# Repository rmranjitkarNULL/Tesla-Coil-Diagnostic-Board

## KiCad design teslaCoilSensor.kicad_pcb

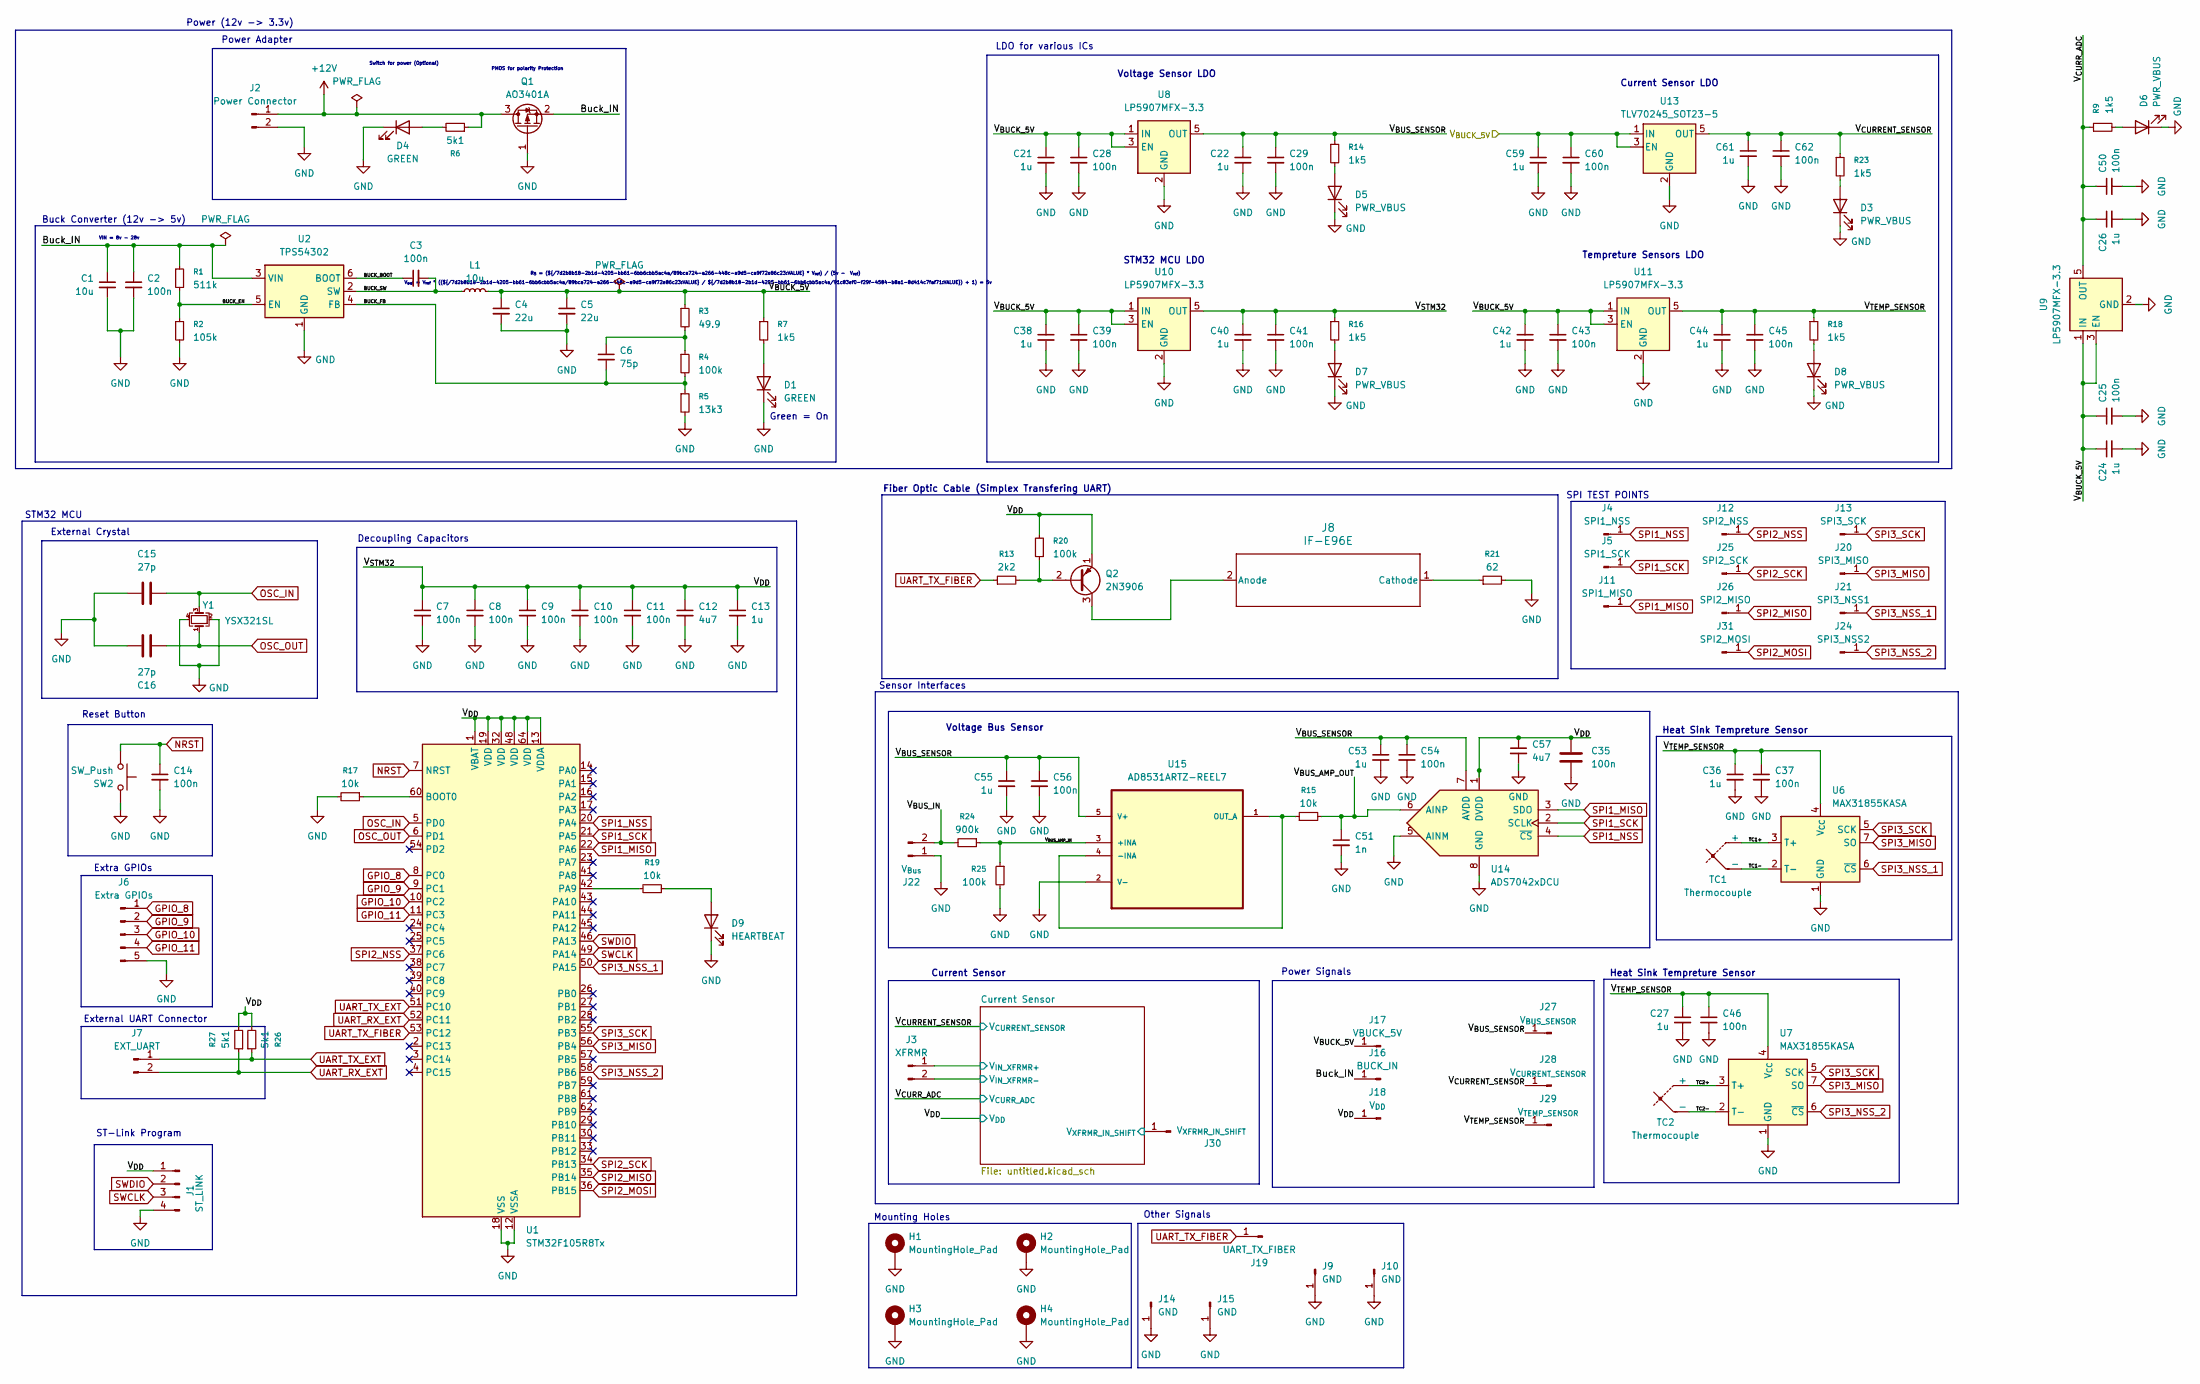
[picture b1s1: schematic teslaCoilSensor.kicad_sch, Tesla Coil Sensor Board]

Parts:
C1: 10u; C_0603_1608Metric
C2, C3, C7, C8, C9, C10, C11, C14, C25, C28, C29, C35, C37, C39, C41, C43, C45, C46, C50, C54, C56, C60, C62: 100n; C_0603_1608Metric
C4, C5: 22u; C_0603_1608Metric
C6: 75p; C_0603_1608Metric
C12, C57: 4u7; C_0603_1608Metric
C13, C21, C22, C24, C26, C27, C36, C38, C40, C42, C44, C53, C55, C59, C61: 1u; C_0603_1608Metric
C15, C16: 27p; C_0603_1608Metric
C51: 1n; C_0603_1608Metric
D1, D4: GREEN; LED_0805_2012Metric
D3, D5, D6, D7, D8: PWR_VBUS; LED_0805_2012Metric
D9: HEARTBEAT; LED_0805_2012Metric
H1, H2, H3, H4: MountingHole_Pad; MountingHole_3.5mm_Pad
J1: ST_LINK; PinHeader_1x04_P2.54mm_Vertical
J2: Power Connector; TerminalBlock_Phoenix_MPT-0,5-2-2.54_1x02_P2.54mm_Horizontal
J3: XFRMR; TerminalBlock_Phoenix_MPT-0,5-2-2.54_1x02_P2.54mm_Horizontal
J4: SPI1_NSS; PinHeader_1x01_P2.54mm_Vertical
J5: SPI1_SCK; PinHeader_1x01_P2.54mm_Vertical
J6: Extra GPIOs; PinHeader_1x05_P2.54mm_Vertical
J7: EXT_UART; TerminalBlock_Phoenix_MPT-0,5-2-2.54_1x02_P2.54mm_Horizontal
J8: IF-E96E; IF-E96E_IFB
J9, J10, J14, J15: GND; PinHeader_1x01_P2.54mm_Vertical
J11: SPI1_MISO; PinHeader_1x01_P2.54mm_Vertical
J12: SPI2_NSS; PinHeader_1x01_P2.54mm_Vertical
J13: SPI3_SCK; PinHeader_1x01_P2.54mm_Vertical
J16: BUCK_IN; PinHeader_1x01_P2.54mm_Vertical
J17: VBUCK_5V; PinHeader_1x01_P2.54mm_Vertical
J18: V_{DD}; PinHeader_1x01_P2.54mm_Vertical
J19: UART_TX_FIBER; PinHeader_1x01_P2.54mm_Vertical
J20: SPI3_MISO; PinHeader_1x01_P2.54mm_Vertical
J21: SPI3_NSS1; PinHeader_1x01_P2.54mm_Vertical
J22: V_{Bus}; TerminalBlock_Phoenix_MPT-0,5-2-2.54_1x02_P2.54mm_Horizontal
J24: SPI3_NSS2; PinHeader_1x01_P2.54mm_Vertical
J25: SPI2_SCK; PinHeader_1x01_P2.54mm_Vertical
J26: SPI2_MISO; PinHeader_1x01_P2.54mm_Vertical
J27: V_{BUS_SENSOR}; PinHeader_1x01_P2.54mm_Vertical
J28: V_{CURRENT_SENSOR}; PinHeader_1x01_P2.54mm_Vertical
J29: V_{TEMP_SENSOR}; PinHeader_1x01_P2.54mm_Vertical
J30: V_{XFRMR_IN_SHIFT}; PinHeader_1x01_P2.54mm_Vertical
J31: SPI2_MOSI; PinHeader_1x01_P2.54mm_Vertical
L1: 10u; SM7850-100MT
Q1: AO3401A; SOT-23
Q2: 2N3906; TO-92_Inline
R1: 511k; R_0603_1608Metric
R2: 105k; R_0603_1608Metric
R3: 49.9; R_0603_1608Metric
R4, R20, R25: 100k; R_0603_1608Metric
R5: 13k3; R_0603_1608Metric
R6, R26, R27: 5k1; R_0603_1608Metric
R7, R9, R14, R16, R18, R23: 1k5; R_0603_1608Metric
R13: 2k2; R_1206_3216Metric
R15, R17, R19: 10k; R_0603_1608Metric
R21: 62; R_0805_2012Metric
R24: 900k; R_Axial_DIN0204_L3.6mm_D1.6mm_P5.08mm_Horizontal
SW2: SW_Push; SW_SPST_PTS647_Sx50
TC1, TC2: Thermocouple; TerminalBlock_Phoenix_MPT-0,5-2-2.54_1x02_P2.54mm_Horizontal
U1: STM32F105R8Tx; LQFP-64_10x10mm_P0.5mm
U2: TPS54302; SOT-23-6
U6, U7: MAX31855KASA; SOIC-8_3.9x4.9mm_P1.27mm
U8, U9, U10, U11: LP5907MFX-3.3; SOT-23-5
U13: TLV70245_SOT23-5; SOT-23-5
U14: ADS7042xDCU; VSSOP-8_2.3x2mm_P0.5mm
U15: AD8531ARTZ-REEL7; SOT95P280X145-5N; MPN AD8531ARTZ-REEL7
Y1: YSX321SL; Crystal_SMD_3225-4Pin_3.2x2.5mm

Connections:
+12V: J2.1, Q1.3 (D), R6.1
/BUCK_BOOT: C3.1, U2.6 (BOOT)
/BUCK_EN: R1.2, R2.1, U2.5 (EN)
/BUCK_FB: C6.2, R4.2, R5.1, U2.4 (FB)
/BUCK_SW: C3.2, L1.1, U2.2 (SW)
/Buck_IN: C1.1, C2.1, J16.1, Q1.2 (S), R1.1, U2.3 (VIN)
/Current Sensor/V_{IN_XFRMR+}: J3.1; also elsewhere on the board
/Current Sensor/V_{XFRMR_IN_SHIFT}: J30.1; also elsewhere on the board
/TC1+: TC1.1 (+), U6.3 (T+)
/TC1-: TC1.2 (-), U6.2 (T-)
/TC2+: TC2.1 (+), U7.3 (T+)
/TC2-: TC2.2 (-), U7.2 (T-)
/V_{BUCK_5V}: C4.1, C5.1, C21.1, C24.1, C25.1, C28.1, C38.1, C39.1, C42.1, C43.1, C59.1, C60.1, J17.1, L1.2, R3.1, R7.1, U8.1 (IN), U8.3 (EN), U9.1 (IN), U9.3 (EN), U10.1 (IN), U10.3 (EN), U11.1 (IN), U11.3 (EN), U13.1 (IN), U13.3 (EN)
/V_{BUS_AMP_IN}: R24.1, R25.1, U15.3 (+INA)
/V_{BUS_AMP_OUT}: C51.1, R15.2, U14.6 (AINP)
/V_{BUS_IN}: J22.2, R24.2
/V_{BUS_SENSOR}: C22.1, C29.1, C53.1, C54.1, C55.1, C56.1, J27.1, R14.1, U8.5 (OUT), U14.7 (AVDD), U15.5 (V+)
/V_{CURRENT_SENSOR}: C61.1, C62.1, J28.1, R23.1, U13.5 (OUT); also elsewhere on the board
/V_{CURR_ADC}: C26.1, C50.1, R9.1, U9.5 (OUT); also elsewhere on the board
/V_{DD}: C7.1, C8.1, C9.1, C10.1, C11.1, C12.1, C13.1, C35.1, C40.1, C41.1, C57.1, J1.1, J18.1, Q2.1 (E), R16.1, R20.2, R26.2, R27.2, U1.1 (VBAT), U1.13 (VDDA), U1.19 (VDD), U1.32 (VDD), U1.48 (VDD), U1.64 (VDD), U10.5 (OUT), U14.1 (DVDD); also elsewhere on the board
/V_{TEMP_SENSOR}: C27.1, C36.1, C37.1, C44.1, C45.1, C46.1, J29.1, R18.1, U6.4 (V_{CC}), U7.4 (V_{CC}), U11.5 (OUT)
GND: C1.2, C2.2, C4.2, C5.2, C7.2, C8.2, C9.2, C10.2, C11.2, C12.2, C13.2, C14.2, C15.1, C16.1, C21.2, C22.2, C24.2, C25.2, C26.2, C27.2, C28.2, C29.2, C35.2, C36.2, C37.2, C38.2, C39.2, C40.2, C41.2, C42.2, C43.2, C44.2, C45.2, C46.2, C50.2, C51.2, C53.2, C54.2, C55.2, C56.2, C57.2, C59.2, C60.2, C61.2, C62.2, D1.1 (K), D3.1 (K), D4.1 (K), D5.1 (K), D6.1 (K), D7.1 (K), D8.1 (K), D9.1 (K), H1.1, H2.1, H3.1, H4.1, J1.4, J2.2, J3.2, J6.5, J9.1, J10.1, J14.1, J15.1, J22.1, Q1.1 (G), R2.2, R5.2, R17.2, R21.2, R25.2, SW2.1, U1.12 (VSSA), U1.18 (VSS), U1.31 (VSS), U1.47 (VSS), U1.63 (VSS), U2.1 (GND), U6.1 (GND), U7.1 (GND), U8.2 (GND), U9.2 (GND), U10.2 (GND), U11.2 (GND), U13.2 (GND), U14.5 (AINM), U14.8 (GND), U15.2 (V-), Y1.2, Y1.4; also elsewhere on the board
GPIO_8: J6.1, U1.8 (PC0)
GPIO_9: J6.2, U1.9 (PC1)
GPIO_10: J6.3, U1.10 (PC2)
GPIO_11: J6.4, U1.11 (PC3)
NRST: C14.1, SW2.2, U1.7 (NRST)
unnamed: C6.1, R3.2, R4.1
unnamed: D1.2 (A), R7.2
unnamed: D3.2 (A), R23.2
unnamed: D4.2 (A), R6.2
unnamed: D5.2 (A), R14.2
unnamed: D6.2 (A), R9.2
unnamed: D7.2 (A), R16.2
unnamed: D8.2 (A), R18.2
unnamed: D9.2 (A), R19.1
unnamed: J8.2 (Anode), Q2.3 (C)
unnamed: J8.1 (Cathode), R21.1
unnamed: Q2.2 (B), R13.2, R20.1
unnamed: R17.1, U1.60 (BOOT0)
unnamed: R19.2, U1.42 (PA9)
unnamed: R15.1, U15.1 (OUT_A), U15.4 (-INA)
OSC_IN: C15.2, U1.5 (PD0), Y1.3
OSC_OUT: C16.2, U1.6 (PD1), Y1.1
SPI1_MISO: J11.1, U1.22 (PA6), U14.3 (SDO)
SPI1_NSS: J4.1, U1.20 (PA4), U14.4 (~CS)
SPI1_SCK: J5.1, U1.21 (PA5), U14.2 (SCLK)
SPI2_MISO: J26.1, U1.35 (PB14); also elsewhere on the board
SPI2_MOSI: J31.1, U1.36 (PB15); also elsewhere on the board
SPI2_NSS: J12.1, U1.37 (PC6); also elsewhere on the board
SPI2_SCK: J25.1, U1.34 (PB13); also elsewhere on the board
SPI3_MISO: J20.1, U1.56 (PB4), U6.7 (SO), U7.7 (SO)
SPI3_NSS_1: J21.1, U1.50 (PA15), U6.6 (~CS)
SPI3_NSS_2: J24.1, U1.58 (PB6), U7.6 (~CS)
SPI3_SCK: J13.1, U1.55 (PB3), U6.5 (SCK), U7.5 (SCK)
SWCLK: J1.3, U1.49 (PA14)
SWDIO: J1.2, U1.46 (PA13)
UART_RX_EXT: J7.2, R27.1, U1.52 (PC11)
UART_TX_EXT: J7.1, R26.1, U1.51 (PC10)
UART_TX_FIBER: J19.1, R13.1, U1.53 (PC12)

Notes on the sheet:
VIN = 8v - 28v
Buck Converter (12v -> 5v)
External UART Connector
Extra GPIOs
Voltage Sensor LDO
STM32 MCU
Tempreture Sensors LDO
PMOS for polarity Protection
ST-Link Program
V_{out} = V_{ref} * ((${/7d2b8b18-2b1d-4205-bb61-6bb6cbb5ac4a/89bca724-a266-448c-a9d5-ca9f72e86c23:VALUE} / ${/7d2b8b18-2b1d-4205-bb61-6bb6cbb5ac4a/91c83ef0-f29f-4584-b8a1-8d414c7faf71:VALUE}) + 1) = 5v
Heat Sink Tempreture Sensor
SPI TEST POINTS
R_{5} = (${/7d2b8b18-2b1d-4205-bb61-6bb6cbb5ac4a/89bca724-a266-448c-a9d5-ca9f72e86c23:VALUE} * V_{ref}) / (5v - V_{ref})
Power (12v -> 3.3v)
Fiber Optic Cable (Simplex Transfering UART)
Mounting Holes
Power Adapter
STM32 MCU LDO
Power Signals
Switch for power (Optional)
Other Signals
Sensor Interfaces
Current Sensor LDO
Current Sensor
External Crystal
LDO for various ICs
Green = On
Reset Button
Decoupling Capacitors
Voltage Bus Sensor

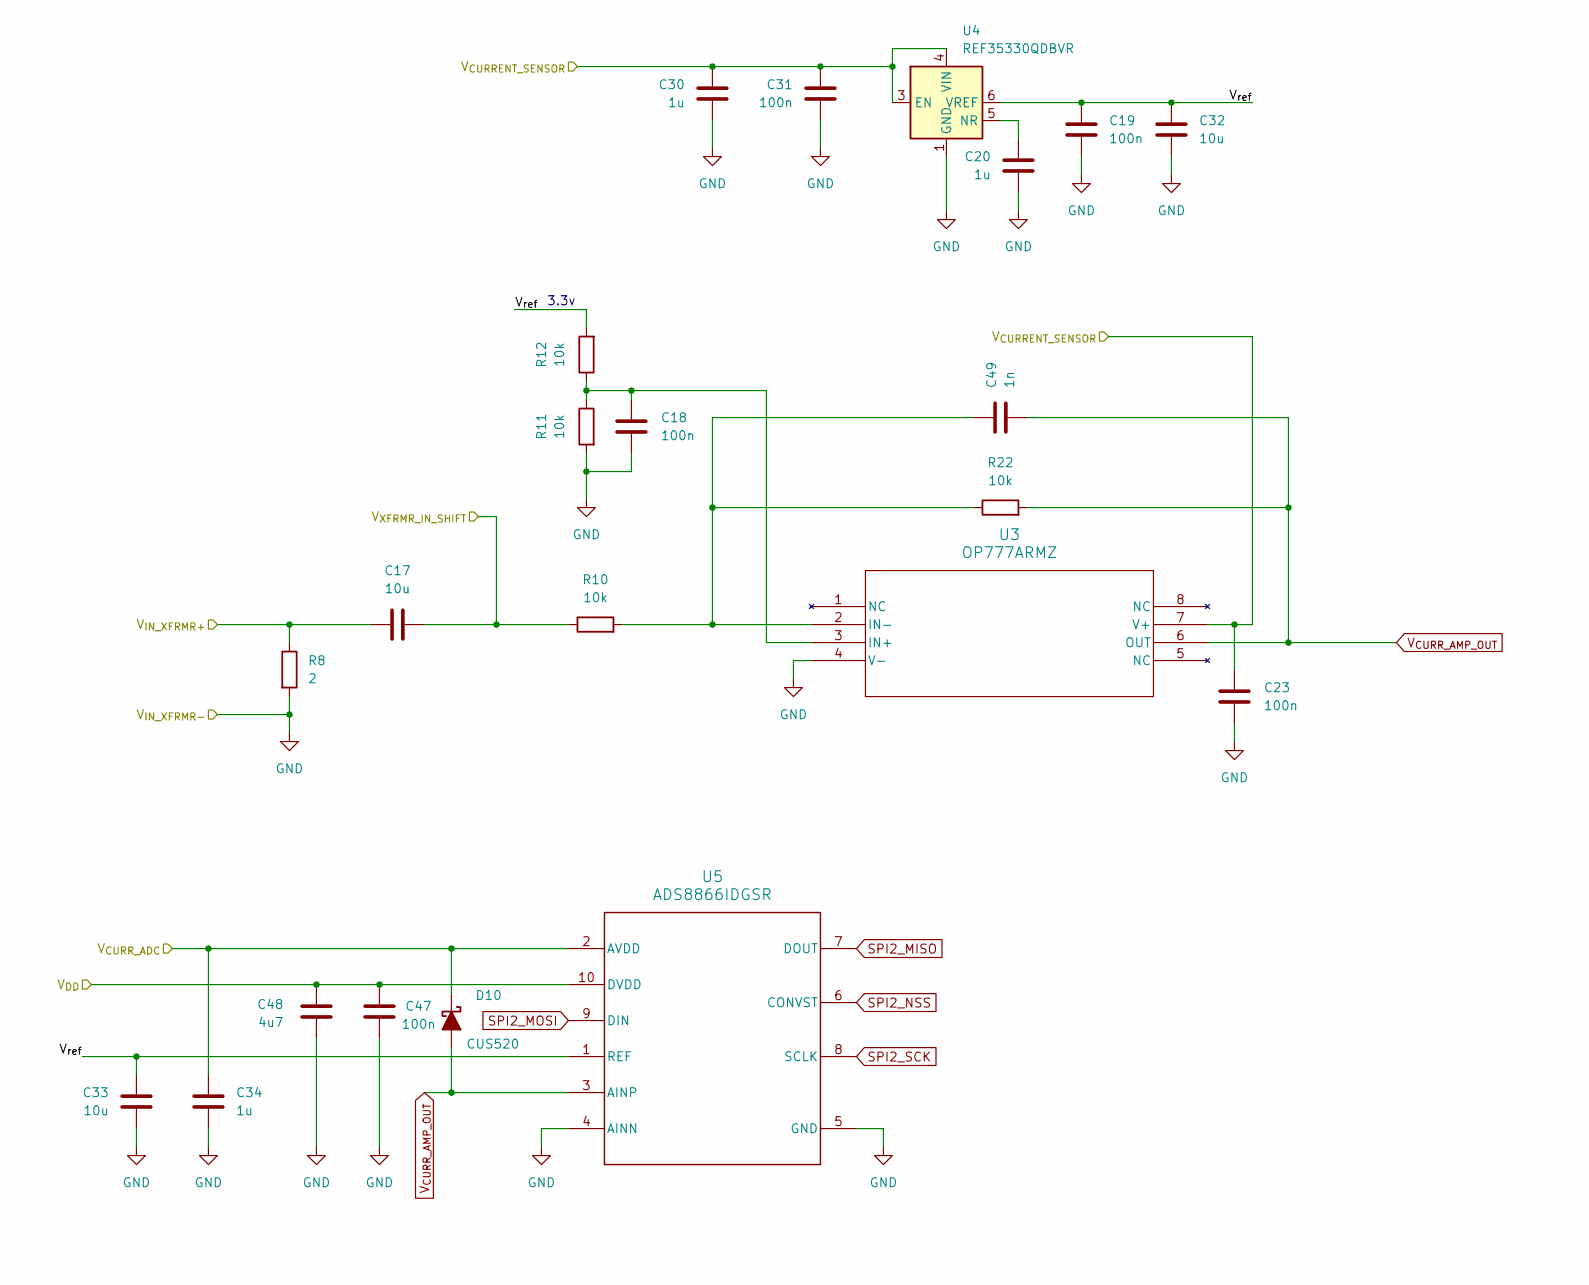
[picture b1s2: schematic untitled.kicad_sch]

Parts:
C17, C32, C33: 10u; C_0603_1608Metric
C18, C19, C23, C31, C47: 100n; C_0603_1608Metric
C20, C30, C34: 1u; C_0603_1608Metric
C48: 4u7; C_0603_1608Metric
C49: 1n; C_0603_1608Metric
D10: CUS520; D_SOD-323
R8: 2; R_1206_3216Metric
R10, R11, R12, R22: 10k; R_0603_1608Metric
U3: OP777ARMZ; R_8_ADI
U4: REF35330QDBVR; SOT-23-6
U5: ADS8866IDGSR; DGS0010A_N

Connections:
/Current Sensor/V_{IN_XFRMR+}: C17.1, R8.1; also elsewhere on the board
/Current Sensor/V_{XFRMR_IN_SHIFT}: C17.2, R10.1; also elsewhere on the board
/Current Sensor/V_{ref}: C19.1, C32.1, C33.1, R12.2, U4.6 (VREF), U5.1 (REF)
/V_{CURRENT_SENSOR}: C23.1, C30.1, C31.1, U3.7 (V+), U4.3 (EN), U4.4 (VIN); also elsewhere on the board
/V_{CURR_ADC}: C34.1, D10.1 (K), U5.2 (AVDD); also elsewhere on the board
/V_{DD}: C47.1, C48.1, U5.10 (DVDD); also elsewhere on the board
GND: C18.2, C19.2, C20.2, C23.2, C30.2, C31.2, C32.2, C33.2, C34.2, C47.2, C48.2, R8.2, R11.2, U3.4 (V-), U4.1 (GND), U4.2 (GND), U5.4 (AINN), U5.5 (GND); also elsewhere on the board
unnamed: C18.1, R11.1, R12.1, U3.3 (IN+)
unnamed: C49.1, R10.2, R22.1, U3.2 (IN-)
unnamed: C20.1, U4.5 (NR)
SPI2_MISO: U5.7 (DOUT); also elsewhere on the board
SPI2_MOSI: U5.9 (DIN); also elsewhere on the board
SPI2_NSS: U5.6 (CONVST); also elsewhere on the board
SPI2_SCK: U5.8 (SCLK); also elsewhere on the board
V_{CURR_AMP_OUT}: C49.2, D10.2 (A), R22.2, U3.6 (OUT), U5.3 (AINP)

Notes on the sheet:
3.3v

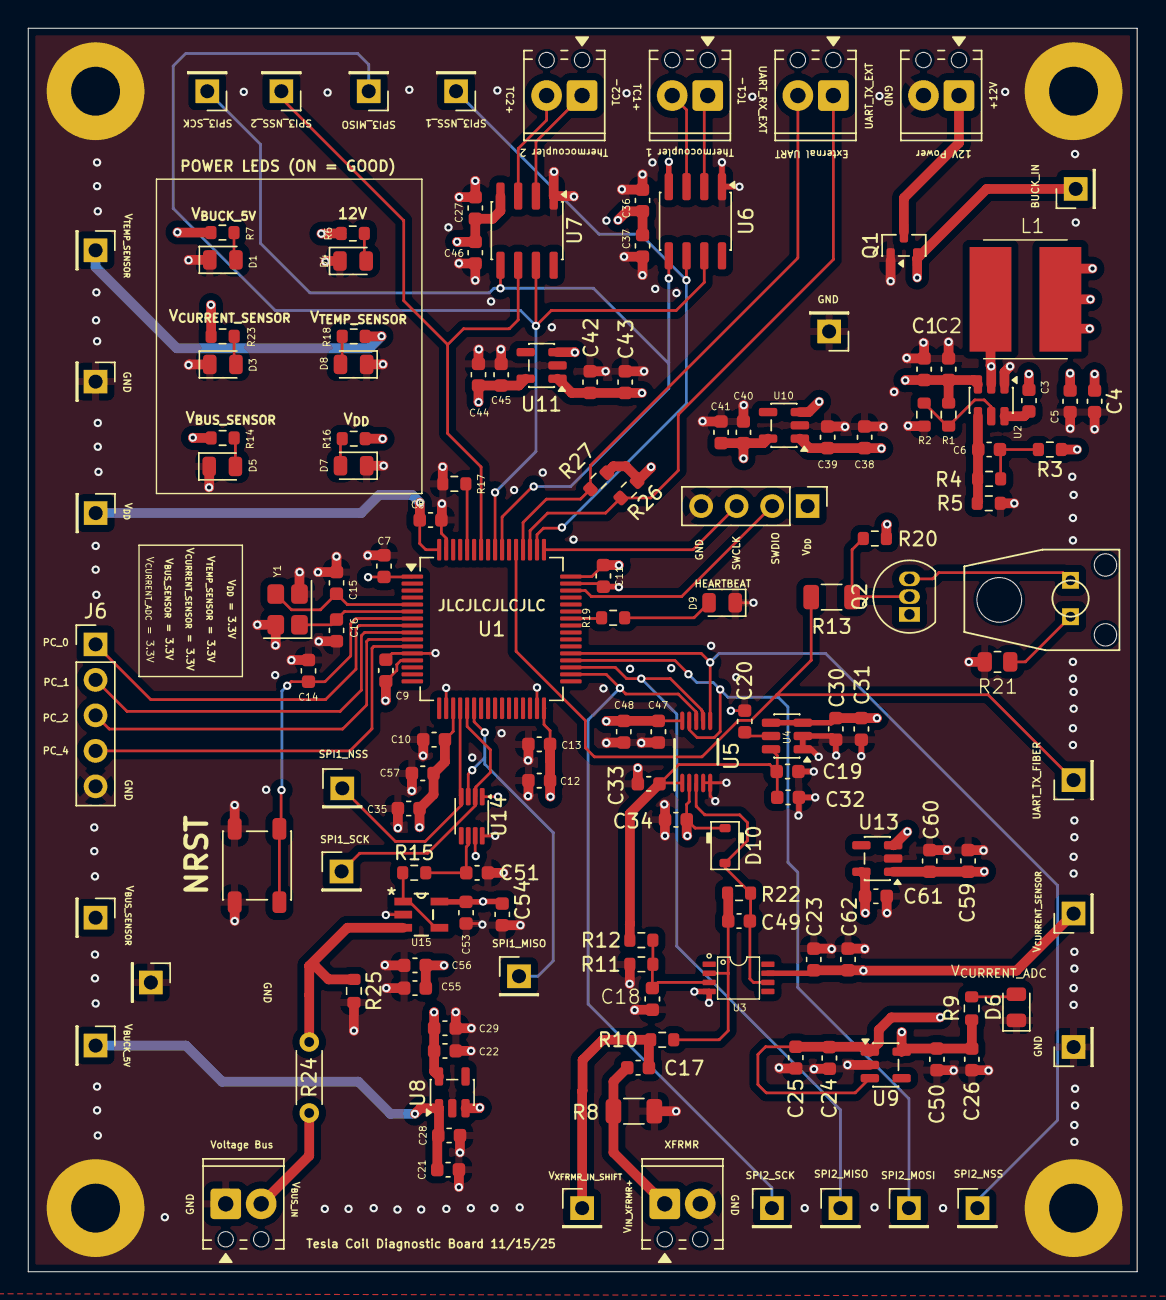
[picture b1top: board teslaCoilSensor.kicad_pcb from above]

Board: 4 copper layers, 79.4 x 89.0 mm, 151 parts (0 on the bottom side), 65 nets.

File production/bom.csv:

Comment,Designator,Footprint,JLCPCB Part #
100k,R25,R_0603_1608Metric,C14675
HeaderMale_1x01_P2.54mm_Vertical,J16,PinHeader_1x01_P2.54mm_Vertical,NA
LP5907MFX-3.3,"U8,U11,U9,U10",SOT-23-5,C22392692
1.5k,"R9,R16,R18,R23,R7,R14",R_0603_1608Metric,C22843
HeaderMale_1x01_P2.54mm_Vertical,J29,PinHeader_1x01_P2.54mm_Vertical,NA
HeaderMale_1x01_P2.54mm_Vertical,J18,PinHeader_1x01_P2.54mm_Vertical,NA
27p,"C16,C15",C_0603_1608Metric,C92670
12MHz,Y1,Crystal_SMD_3225-4Pin_3.2x2.5mm,C9002
100n,"C3,C31,C37,C29,C45,C28,C7,C9,C39,C23,C62,C2,C47,C19,C46,C8,C50,C56,C18,C14,C54,C41,C10,C43,C60,C25,C35,C11",C_0603_1608Metric,C14663
Screw Terminal,"TC1,TC2","TerminalBlock_Phoenix_MPT-0,5-2-2.54_1x02_P2.54mm_Horizontal",C3029316
5.1k,"R6,R26,R27",R_0603_1608Metric,C23186
10k,"R11,R10,R19,R12,R17,R22,R15",R_0603_1608Metric,C25804
REF35330QDBVR,U4,SOT-23-6,C7467076
HeaderMale_1x01_P2.54mm_Vertical,J24,PinHeader_1x01_P2.54mm_Vertical,NA
HeaderMale_1x01_P2.54mm_Vertical,J28,PinHeader_1x01_P2.54mm_Vertical,NA
900k,R24,R_Axial_DIN0204_L3.6mm_D1.6mm_P5.08mm_Horizontal,NA
1u,"C26,C13,C53,C59,C42,C30,C38,C36,C21,C40,C34,C22,C44,C61,C55,C27,C24,C20",C_0603_1608Metric,C15849
STM32F105R8T6,U1,LQFP-64_10x10mm_P0.5mm,C80986
10u,"C32,C1,C33,C17",C_0603_1608Metric,C96446
IF-E96,J8,IF-E96E_IFB,NA
Green LED,"D1,D4",LED_0805_2012Metric,C25170728
Screw Terminal,J22,"TerminalBlock_Phoenix_MPT-0,5-2-2.54_1x02_P2.54mm_Horizontal",C3029316
ADS7042xDCU,U14,VSSOP-8_2.3x2mm_P0.5mm,C701641
Green LED,"D8,D7,D5,D3,D6",LED_0805_2012Metric,C25170728
100n,C6,C_0603_1608Metric,C14663
HeaderMale_1x01_P2.54mm_Vertical,J11,PinHeader_1x01_P2.54mm_Vertical,NA
10u,L1,SM7850-100MT,C9182
Screw Terminal,J2,"TerminalBlock_Phoenix_MPT-0,5-2-2.54_1x02_P2.54mm_Horizontal",C3029316
Green LED,D9,LED_0805_2012Metric,C25170728
HeaderMale_1x01_P2.54mm_Vertical,J25,PinHeader_1x01_P2.54mm_Vertical,NA
10k,R1,R_0603_1608Metric,C25804
MAX31855KASA,"U6,U7",SOIC-8_3.9x4.9mm_P1.27mm,C52028
62,R21,R_0805_2012Metric,C17784
HeaderMale_1x01_P2.54mm_Vertical,J6,PinHeader_1x05_P2.54mm_Vertical,NA
100k,"R20,R4",R_0603_1608Metric,C14675
HeaderMale_1x01_P2.54mm_Vertical,J12,PinHeader_1x01_P2.54mm_Vertical,NA
4.7u,"C48,C57,C12",C_0603_1608Metric,C19666
105k,R2,R_0603_1608Metric,C16840
13.3k,R5,R_0603_1608Metric,C25952
HeaderMale_1x01_P2.54mm_Vertical,J30,PinHeader_1x01_P2.54mm_Vertical,NA
1n,"C51,C49",C_0603_1608Metric,C1588
AD8531ARTZ-REEL7,U15,SOT95P280X145-5N,C143905
HeaderMale_1x01_P2.54mm_Vertical,J31,PinHeader_1x01_P2.54mm_Vertical,NA
HeaderMale_1x01_P2.54mm_Vertical,J17,PinHeader_1x01_P2.54mm_Vertical,NA
HeaderMale_1x01_P2.54mm_Vertical,J26,PinHeader_1x01_P2.54mm_Vertical,NA
CUS520,D10,D_SOD-323,C324473
TLV70245_SOT23-5,U13,SOT-23-5,C66350
Screw Terminal,J7,"TerminalBlock_Phoenix_MPT-0,5-2-2.54_1x02_P2.54mm_Horizontal",C3029316
Screw Terminal,J3,"TerminalBlock_Phoenix_MPT-0,5-2-2.54_1x02_P2.54mm_Horizontal",C3029316
HeaderMale_1x01_P2.54mm_Vertical,J1,PinHeader_1x04_P2.54mm_Vertical,NA
HeaderMale_1x01_P2.54mm_Vertical,J4,PinHeader_1x01_P2.54mm_Vertical,NA
HeaderMale_1x01_P2.54mm_Vertical,"J14,J9,J10,J15",PinHeader_1x01_P2.54mm_Vertical,NA
HeaderMale_1x01_P2.54mm_Vertical,J20,PinHeader_1x01_P2.54mm_Vertical,NA
HeaderMale_1x01_P2.54mm_Vertical,J5,PinHeader_1x01_P2.54mm_Vertical,NA
HeaderMale_1x01_P2.54mm_Vertical,J19,PinHeader_1x01_P2.54mm_Vertical,NA
2.2k,R13,R_1206_3216Metric,C17948
Push Button,SW2,SW_SPST_PTS647_Sx50,NA
49.9,R3,R_0603_1608Metric,C23185
2N3906,Q2,TO-92_Inline,C9809
1n,"C5,C4",C_0603_1608Metric,C1588
HeaderMale_1x01_P2.54mm_Vertical,J13,PinHeader_1x01_P2.54mm_Vertical,NA
HeaderMale_1x01_P2.54mm_Vertical,J21,PinHeader_1x01_P2.54mm_Vertical,NA
OP777ARMZ,U3,R_8_ADI,C690987
HeaderMale_1x01_P2.54mm_Vertical,J27,PinHeader_1x01_P2.54mm_Vertical,NA
TPS54302,U2,SOT-23-6,C311983
ADS8866IDGSR,U5,DGS0010A_N,C455432
AO3401A,Q1,SOT-23,C15127
2,R8,R_1206_3216Metric,NA

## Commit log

2025-11-25 Adding initial files
2025-11-25 Added git ignore
2025-11-25 Made file system changes
